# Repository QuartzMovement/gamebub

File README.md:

<p align="center">
  
</p>

**Game Bub** is an open-source FPGA retro emulation handheld, with support for Game Boy, Game Boy Color, and Game Boy Advance games.

You can buy your own, prebuilt Game Bub from **[Crowd Supply](https://www.crowdsupply.com/second-bedroom/game-bub)**!

You can find the [user guide and documentation here](https://docs.gamebub.net/).

Want to chat about Game Bub? Feel free to [join the Discord](https://discord.gg/T5xrYpMfN7).

Check out the [announcement blog post](https://eli.lipsitz.net/posts/introducing-gamebub/) for an in-depth look at the development process!

## Features
* Play physical Game Boy / Color / Advance cartridges
* Load and play ROM files from a microSD card (with built-in support for rumble, clock, accelerometer, gyroscope)
* Multiplayer link cable functionality
* Custom, from-scratch Game Boy and Game Boy Advance FPGA cores with great game compatibility
* 14+ hour battery life 
* Video output to TV or monitor via Game Bub Dock
* Extensible hardware, designed for future improvements

## Building

Building a Game Bub handheld requires manufacturing PCBs, 3D printing the shell and buttons, and assembling components from a variety of sources. For information on manufacturing and assembling your own, see [docs/building.md](docs/building.md).

For other inquiries, contact us at support@gamebub.net.

## Architecture

For an in-depth description of the project architecture, see [docs/architecture.md](docs/architecture.md).

The Game Bub handheld consists of a Xilinx XC7A100T FPGA to do the main emulation and I/O, and an ESP32-S3 microcontroller to do auxiliary tasks (configuring the FPGA, rendering the UI, loading ROM files from a microSD card and sending it to the FPGA).

### Directory Structure

* `fpga`: FPGA source code (HDL), written in [Chisel](https://github.com/chipsalliance/chisel)
* `firmware`: Microcontroller firmware

## License

Unless otherwise specified:

* Firmware (in `firmware/`) and scripts (in `scripts/`) are licensed under GPLv3 (`GPL-3.0-only`).
* FPGA source code (in `fpga/`) is licensed under the CERN Open Hardware License Version 2 - Strongly Reciprocal (`CERN-OHL-S-2.0`)
* PCB (schematic and layout), mechanical, and hardware design files are licensed under the CERN Open Hardware License Version 2 - Strongly Reciprocal (`CERN-OHL-S-2.0`)

At a high level, this means that you can copy, share, and modify the source code, as long as you provide proper attribution and share your source code / design files with the same license. However, the "Game Bub" name and logo are trademarked, and you may not use them for your product without permission.

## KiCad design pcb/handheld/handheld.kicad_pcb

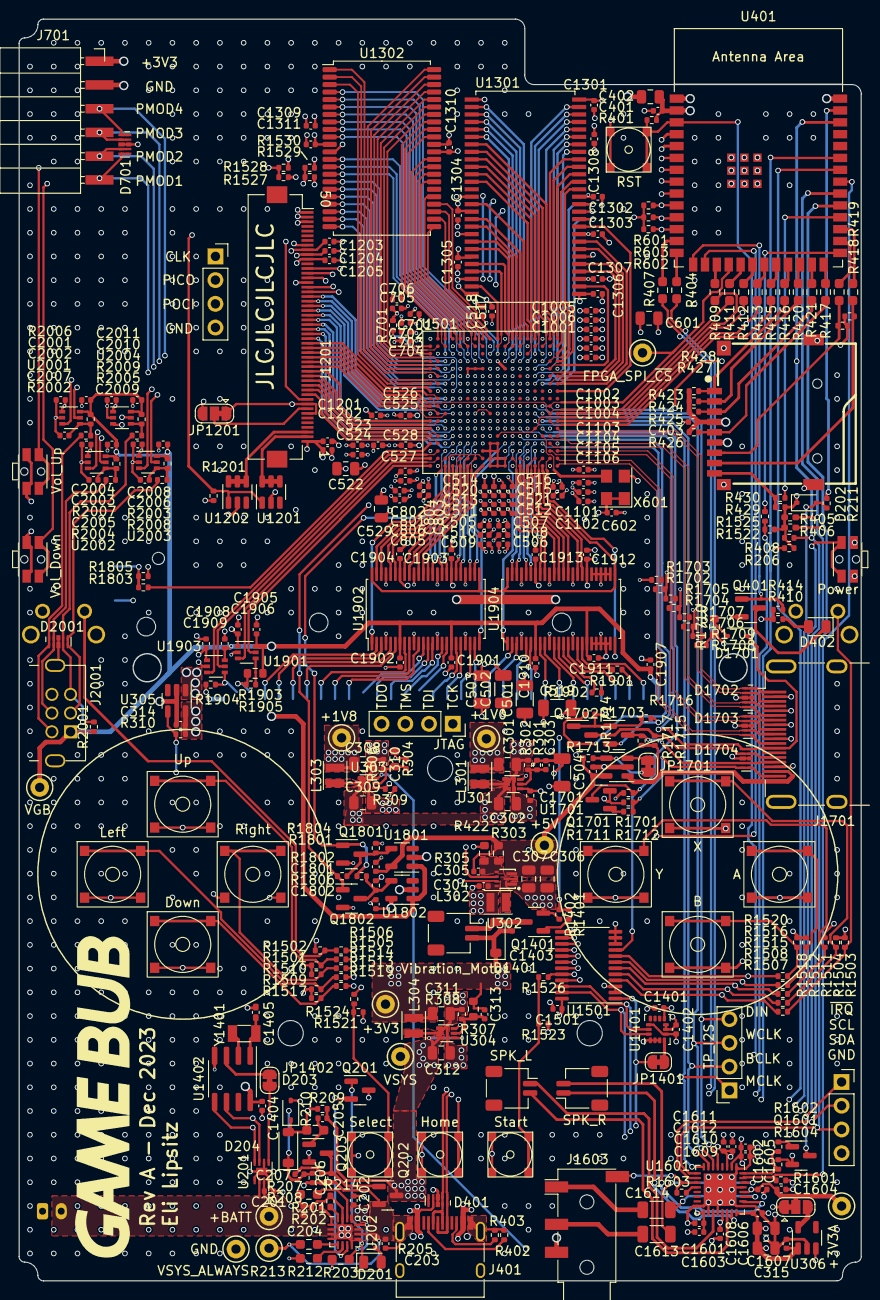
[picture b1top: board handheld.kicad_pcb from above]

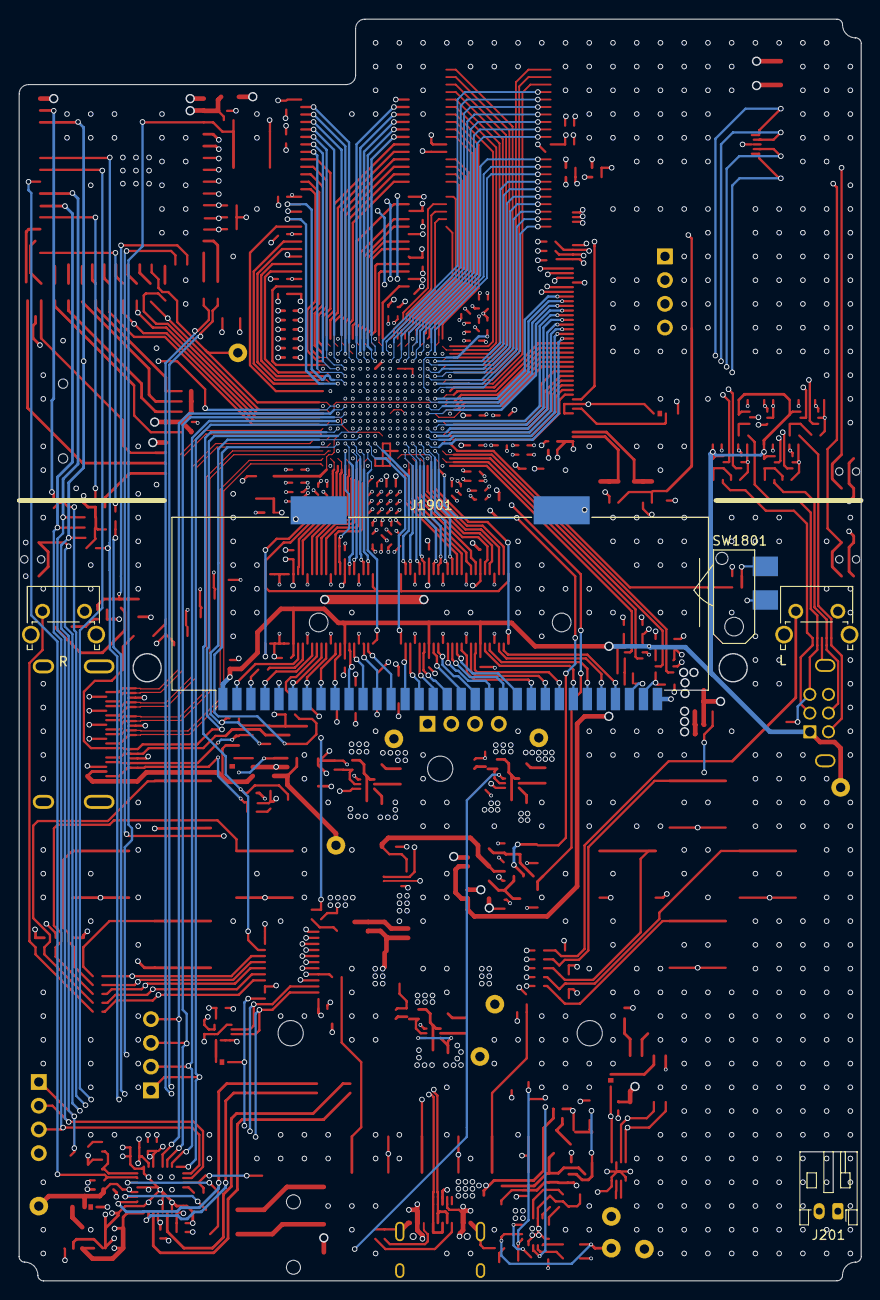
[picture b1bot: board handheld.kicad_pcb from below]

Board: 6 copper layers, 90.1 x 135.0 mm, 386 parts (5 on the bottom side), 364 nets.

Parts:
C201, C206, C314, C401, C403, C602, C1201, C1202, C1203, C1204, C1205, C1301, C1302, C1303, C1304, C1305, C1306, C1307, C1310, C1311, C1401, C1402, C1403, C1404, C1501, C1602, C1604, C1606, C1608, C1610, C1612, C1701, C1801, C1802, C1901, C1902, C1903, C1904, C1905, C1906, C1907, C1908, C1909, C1910, C1911, C1912, C1913, C2001, C2002, C2003, C2004, C2008, C2009, C2010, C2011: 100n; C_0402_1005Metric
C202, C203, C204, C505, C506, C507, C508, C509, C510, C523, C524, C705, C706, C805, C806, C1005, C1006, C1105, C1106: 4u7; C_0402_1005Metric
C205, C304, C315, C1308, C1309, C1601, C1603, C1609, C1611: 10u; C_0402_1005Metric
C207: 1u; C_0402_1005Metric
C301, C302, C308, C309, C311, C312, C522, C529, C601: 47u; C_0805_2012Metric
C303, C310, C313: 22p; C_0402_1005Metric
C305: 470p; C_0402_1005Metric
C306, C307, C402, C1605, C1607: 22u; C_0805_2012Metric
C501, C502, C503, C504, C519, C1613, C1614: 100u; C_1206_3216Metric
C511, C512, C513, C514, C515, C516, C517, C518, C520, C521, C525, C526, C527, C528, C701, C702, C703, C704, C801, C802, C803, C804, C1001, C1002, C1003, C1004, C1101, C1102, C1103, C1104: 470n; C_0402_1005Metric
C1405: 22p; C_0402_1005Metric_Pad0.74x0.62mm_HandSolder
C2005, C2006, C2007: 100p; C_0402_1005Metric
D201: CHARGE_LED; LED_0805_2012Metric
D202, D203, D1701: D_Schottky; D_SOD-323
D204, D1401: 1N4148W; D_SOD-123
D401, D701, D1702, D1703, D1704, D2001: H5VU25U; Diodes_UDFN-10_1.0x2.5mm_P0.5mm
D402: STATUS_LED; LED_0805_2012Metric
H101, H102, H103: MountingHole; MountingHole_2.7mm_M2.5
J201: Batt_Conn; JST_PH_S2B-PH-K_1x02_P2.00mm_Horizontal
J401: USB_C_Receptacle_USB2.0; USB_C_Receptacle_HRO_TYPE-C-31-M-12
J402: Micro_SD_Card_Det1; microSD_G-Switch_GT-TF003-H0185-02
J403: TP_I2C; PinSocket_1x04_P2.54mm_Vertical
J404: TP_SPI; PinSocket_1x04_P2.54mm_Vertical
J601: JTAG; PinSocket_1x04_P2.54mm_Vertical
J701: PMOD; PinSocket_1x06_P2.54mm_Horizontal_SMD
J1201: Hirose_FH12S-50S-0.5SH_1x50-1MP_P0.50mm_Horizontal_FLIPPED
J1401: Vibration_Motor; JST_SH_SM02B-SRSS-TB_1x02-1MP_P1.00mm_Horizontal
J1601: SPK_L; JST_SH_SM02B-SRSS-TB_1x02-1MP_P1.00mm_Horizontal
J1602: SPK_R; JST_SH_SM02B-SRSS-TB_1x02-1MP_P1.00mm_Horizontal
J1603: Headphone Jack; Jack_3.5mm_PJ320D_Horizontal
J1604: TP_I2S; PinSocket_1x04_P2.54mm_Vertical
J1701: HDMI_A; HDMI_A_Molex_208658-1001_Horizontal
J1901: Cartridge_Slot; GameBoy_Cartridge_AGS_1x32-1MP_P1.50mm_Socket_Horizontal
J2001: Link_Port; GameBoy_LinkPort_AGB_Horizontal
JP301: 3V3A_Jumper; SolderJumper-3_P1.3mm_Bridged12_RoundedPad1.0x1.5mm
JP1201: SolderJumper_3_Bridged12; SolderJumper-3_P1.3mm_Bridged12_RoundedPad1.0x1.5mm
JP1401, JP1402, JP1701: SolderJumper_2_Bridged; SolderJumper-2_P1.3mm_Bridged_RoundedPad1.0x1.5mm
L301, L302, L303, L304: 1u; L_Sunlord_SWPA252012S
Q201, Q203, Q401, Q1401, Q1601, Q1701, Q1702, Q1703, Q1801, Q1802: AO3400A; SOT-23
Q202: AO3401A; SOT-23
R201: 47K; R_0603_1608Metric_Pad0.98x0.95mm_HandSolder
R202, R207, R301, R401, R408, R422, R423, R424, R425, R426, R427, R428, R429, R430, R1201, R1402, R1501, R1502, R1503, R1504, R1505, R1506, R1507, R1508, R1509, R1510, R1511, R1512, R1513, R1514, R1515, R1516, R1517, R1518, R1519, R1520, R1521, R1522, R1523, R1524, R1525, R1526, R1527, R1528, R1529, R1530, R1604, R1711, R1712, R1801, R1803, R1804, R1805, R2006, R2007, R2008, R2009: 10K; R_0402_1005Metric
R203: 1K1; R_0603_1608Metric_Pad0.98x0.95mm_HandSolder
R205, R410, R1603: 2K2; R_0402_1005Metric
R206, R208, R209, R309, R310, R414, R1601, R1713, R1802, R1806, R1904, R2001: 100K; R_0402_1005Metric
R210: 470K; R_0603_1608Metric_Pad0.98x0.95mm_HandSolder
R211, R701, R1401, R1602, R1714, R1716: 1K; R_0402_1005Metric
R212, R213, R404, R407, R409, R411, R412, R413, R415, R416, R417, R418, R419, R420, R421: 0R; R_0603_1608Metric_Pad0.98x0.95mm_HandSolder
R214: 1K; R_0402_1005Metric_Pad0.72x0.64mm_HandSolder
R302, R306, R308: 15K; R_0402_1005Metric
R303: 220K; R_0603_1608Metric
R304, R305: 30K; R_0603_1608Metric
R307: 68K; R_0603_1608Metric
R402, R403: 5K1; R_0402_1005Metric
R405, R406: 3K3; R_0402_1005Metric_Pad0.72x0.64mm_HandSolder
R601, R602, R603, R1701: 4K7; R_0402_1005Metric
R1702, R1703, R1704, R1705, R1706, R1707, R1708, R1709, R1901, R1902, R1905: 49R9; R_0402_1005Metric
R1710, R1903: 27K; R_0603_1608Metric
R1715, R1717: 1K5; R_0402_1005Metric
R2002, R2003, R2004, R2005: 330R; R_0402_1005Metric
SW201: Power; SW_SPST_SKSC
SW401: RST; SW_SPST_SKRB
SW1501: Up; SW_SPST_SKRR
SW1502: L; SW_Tactile_SPST_Angled_TL1105VFxxxx
SW1503: R; SW_Tactile_SPST_Angled_TL1105VFxxxx
SW1504: X; SW_SPST_SKRR
SW1505: Left; SW_SPST_SKRR
SW1506: Right; SW_SPST_SKRR
SW1507: Y; SW_SPST_SKRR
SW1508: A; SW_SPST_SKRR
SW1509: Down; SW_SPST_SKRR
SW1510: B; SW_SPST_SKRR
SW1511: Select; SW_SPST_SKRB
SW1512: Home; SW_SPST_SKRB
SW1513: Start; SW_SPST_SKRB
SW1514: Vol_Up; SW_SPST_SKSC
SW1515: Vol_Down; SW_SPST_SKSC
SW1801: SW_Cartridge; JJOV0UL650NONPRBK_SIDE
TP201: +BATT; TestPoint_Keystone_5000-5004_Miniature
TP202: VSYS_ALWAYS; TestPoint_Keystone_5000-5004_Miniature
TP203: VSYS; TestPoint_Keystone_5000-5004_Miniature
TP301: +1V0; TestPoint_Keystone_5000-5004_Miniature
TP302: +1V8; TestPoint_Keystone_5000-5004_Miniature
TP303: +3V3; TestPoint_Keystone_5000-5004_Miniature
TP304: +3V3A; TestPoint_Keystone_5000-5004_Miniature
TP305: +5V; TestPoint_Keystone_5000-5004_Miniature
TP306: GND; TestPoint_Keystone_5000-5004_Miniature
TP401: FPGA_SPI_~{CS}; TestPoint_Keystone_5000-5004_Miniature
TP1801: VGB; TestPoint_Keystone_5000-5004_Miniature
U201: MAX17048; TDFN-8-1EP_2x2mm_P0.5mm_EP0.8x1.2mm
U202: BQ24073RGT; VQFN-16-1EP_3x3mm_P0.5mm_EP1.6x1.6mm
U301, U303, U304: TLV62585PDRL; SOT-563
U302: TPS61022RWUR; VQFN-7_L2.0-W2.0-P0.55-TL_RWU
U305, U1701, U1801, U1802: AP2191W; SOT-23-5
U306: LP5907MFX-3.3; SOT-23-5
U401: ESP32-S3-WROOM-1
U501: XC7A100T-CSG324; Xilinx_CSG324
U1201, U1202: AP2502; SOT-23-6
U1301: W9825G6KH-6; TSOP-II-54_22.2x10.16mm_P0.8mm
U1302: IS61WV25616EDBLL-10TLI; TSOP-II-44_10.16x18.41mm_P0.8mm
U1401: LSM6DS3TR-C; LGA-14_3x2.5mm_P0.5mm_LayoutBorder3x4y
U1402: PCF8563T; SOIC-8_3.9x4.9mm_P1.27mm
U1501: TCA9535PWR; TSSOP-24_4.4x7.8mm_P0.65mm
U1601: TLV320DAC3101; VQFN-32-1EP_5x5mm_P0.5mm_EP3.5x3.5mm
U1901, U1903, U2001, U2002, U2003, U2004: 74LVC1T45; SOT-363_SC-70-6
U1902, U1904: 74LVCH16T245; TSSOP-48_6.1x12.5mm_P0.5mm
X601: YSO110TR 50MHz; Oscillator_SMD_SeikoEpson_SG8002CE-4Pin_3.2x2.5mm
Y1401: 32.768kHz; Crystal_SMD_3215-2Pin_3.2x1.5mm

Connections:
+1V0: C301.1, C303.2, C501.1, C502.1, C503.1, C504.1, C505.1, C506.1, C507.1, C508.1, C509.1, C510.1, C511.1, C512.1, C513.1, C514.1, C515.1, C516.1, C517.1, C518.1, C519.1, C520.1, C521.1, L301.2, R301.1, TP301.1, U501.F8 (VCCINT), U501.F10 (VCCBRAM), U501.G7 (VCCINT), U501.G9 (VCCINT), U501.G11 (VCCBRAM), U501.H8 (VCCINT), U501.J7 (VCCINT), U501.J11 (VCCINT), U501.K8 (VCCINT), U501.L7 (VCCINT), U501.L11 (VCCINT), U501.M8 (VCCINT), U501.M10 (VCCINT), U501.N7 (VCCINT), U501.N9 (VCCINT), U501.N11 (VCCINT)
+1V8: C308.1, C310.2, C522.1, C523.1, C524.1, C525.1, C526.1, C527.1, C528.1, C1609.1, C1610.2, L303.2, R304.1, TP302.1, U501.F12 (VCCAUX), U501.H10 (VCCADC_0), U501.H12 (VCCAUX), U501.K12 (VCCAUX), U501.M12 (VCCAUX), U1601.3 (DVDD)
+3V3: C311.1, C313.2, C314.2, C401.2, C402.1, C403.2, C1201.2, C1202.2, C1203.2, C1204.2, C1205.2, C1401.1, C1402.2, C1403.2, C1501.1, C1802.2, D202.1 (K), D1401.1 (K), J402.4 (VDD), J1201.1 (LEDA), J1201.7 (IM0), J1201.9 (IM2), J1201.40 (VDDI), J1201.41 (VDDI), J1201.42 (VCI), J1401.2, JP1201.1 (A), L304.2, R206.1, R307.1, R310.1, R401.1, R405.1, R406.1, R408.1, R410.1, R414.1, R423.1, R424.1, R425.1, R426.1, R427.1, R428.1, R429.2, R1501.1, R1502.1, R1503.1, R1504.1, R1509.1, R1510.1, R1511.1, R1512.1, R1517.1, R1518.1, R1521.1, R1522.1, R1523.1, R1527.1, R1529.1, TP303.1, U305.5 (IN), U401.2 (3V3), U1401.5 (VDDIO), U1401.8 (VDD), U1401.12 (CS), U1501.24 (VCC), U1802.5 (IN)
+3V3A_DAC: C1601.1, C1602.2, C1603.1, C1604.2, JP301.2 (C), TP304.1, U1601.17 (AVDD), U1601.28 (HPVDD)
+3V3_FPGA: C529.1, C601.1, C602.2, C701.1, C702.1, C703.1, C704.1, C705.1, C706.1, C801.1, C802.1, C803.1, C804.1, C805.1, C806.1, C1001.1, C1002.1, C1003.1, C1004.1, C1005.1, C1006.1, C1101.1, C1102.1, C1103.1, C1104.1, C1105.1, C1106.1, C1301.2, C1302.2, C1303.2, C1304.2, C1305.2, C1306.2, C1307.2, C1308.1, C1309.1, C1310.2, C1311.2, C1611.1, C1612.2, C1903.2, C1904.2, C1906.2, C1909.2, C1912.2, C1913.2, C2002.2, C2004.2, C2009.2, C2011.2, J701.1, JP301.1 (A), Q1702.1 (G), Q1703.1 (G), R601.2, R602.2, R603.2, R701.2, R1701.2, R1702.1, R1703.1, R1704.1, R1705.1, R1706.1, R1707.1, R1708.1, R1709.1, R1710.1, R1714.2, R1716.2, R1904.1, SW1801.2 (B), U305.1 (OUT), U501.A7 (VCCO_35), U501.A17 (VCCO_15), U501.C3 (VCCO_35), U501.C13 (VCCO_15), U501.D6 (VCCO_35), U501.D16 (VCCO_15), U501.F2 (VCCO_35), U501.G5 (VCCO_35), U501.G15 (VCCO_15), U501.H18 (VCCO_15), U501.J1 (VCCO_35), U501.K4 (VCCO_34), U501.K14 (VCCO_15), U501.L17 (VCCO_14), U501.N3 (VCCO_34), U501.N13 (VCCO_14), U501.P6 (VCCO_34), U501.P8 (CFGBVS_0), U501.P11 (M2_0), U501.P12 (M0_0), U501.P13 (M1_0), U501.P16 (VCCO_14), U501.R9 (VCCO_0), U501.T2 (VCCO_34), U501.T12 (VCCO_14), U501.U5 (VCCO_34), U501.U15 (VCCO_14), U501.V8 (VCCO_34), U501.V18 (VCCO_14), U1301.1 (VDD), U1301.3 (VDDQ), U1301.9 (VDDQ), U1301.14 (VDD), U1301.27 (VDD), U1301.43 (VDDQ), U1301.49 (VDDQ), U1302.11 (VDD), U1302.33 (VDD), U1601.2 (IOVDD), U1901.1 (VCCA), U1902.31 (VCCA), U1902.42 (VCCA), U1903.1 (VCCA), U1904.31 (VCCA), U1904.42 (VCCA), U2001.1 (VCCA), U2002.1 (VCCA), U2003.1 (VCCA), U2004.1 (VCCA), X601.1 (Tri-State), X601.4 (VDD)
+3V3_PG: R401.2, SW401.2, U304.6 (PG), U401.3 (EN)
+5V: C305.2, C306.1, C307.1, C1701.2, C1801.2, R303.1, R1713.1, TP305.1, U302.3 (VOUT), U1701.5 (IN), U1801.5 (IN)
+BATT: C201.2, C204.1, J201.2, TP201.1, U201.2 (CELL), U201.3 (VDD), U202.2 (BAT), U202.3 (BAT)
/Audio/DAC_INT: R1602.2, R1604.1, U1601.32 (GPIO1)
/Audio/DAC_INT_R: Q1601.1 (G), R1602.1
/Audio/HeadphoneJack_Tip: C1614.2, J1603.T
/Audio/Headphone_Jack_R: C1613.2, J1603.R1
/Audio/Headphone_Left: C1614.1, U1601.27 (HPL)
/Audio/Headphone_Mic: J1603.S, R1603.2, U1601.11 (VOL/MICDET)
/Audio/Headphone_Right: C1613.1, U1601.30 (HPR)
/Audio/MICBIAS: R1603.1, U1601.12 (MICBIAS)
/Audio/Speaker_Left_M: J1601.1, U1601.19 (SPLM)
/Audio/Speaker_Left_P: J1601.2, U1601.22 (SPLP)
/Audio/Speaker_Right_M: J1602.1, U1601.23 (SPRM)
/Audio/Speaker_Right_P: J1602.2, U1601.26 (SPRP)
/Buttons/BTN_A_s: R1512.2, R1516.2, SW1508.1
/Buttons/BTN_B_s: R1518.2, R1520.2, SW1510.1
/Buttons/BTN_Down_s: R1517.2, R1519.2, SW1509.1
/Buttons/BTN_Home_s: R1522.2, R1525.2, SW1512.1
/Buttons/BTN_L_s: R1502.2, R1506.2, SW1502.1
/Buttons/BTN_Left_s: R1509.2, R1513.2, SW1505.1
/Buttons/BTN_R_s: R1503.2, R1507.2, SW1503.1
/Buttons/BTN_Right_s: R1510.2, R1514.2, SW1506.1
/Buttons/BTN_Select_s: R1521.2, R1524.2, SW1511.1
/Buttons/BTN_Start_s: R1523.2, R1526.2, SW1513.1
/Buttons/BTN_Up_s: R1501.2, R1505.2, SW1501.1
/Buttons/BTN_Vol_Down_s: R1529.2, R1530.2, SW1515.1
/Buttons/BTN_Vol_Up_s: R1527.2, R1528.2, SW1514.1
/Buttons/BTN_X_s: R1504.2, R1508.2, SW1504.1
/Buttons/BTN_Y_s: R1511.2, R1515.2, SW1507.1
/ESP32-S3/ESP32_SDIO_CLK: R417.1, U401.26 (GPIO45)
/ESP32-S3/ESP32_SDIO_CMD: R421.1, U401.25 (GPIO48)
/ESP32-S3/ESP32_SDIO_D0: R418.2, U401.28 (GPIO35)
/ESP32-S3/ESP32_SDIO_D1: R419.2, U401.29 (GPIO36)
/ESP32-S3/ESP32_SDIO_D2: R416.1, U401.23 (GPIO21)
/ESP32-S3/ESP32_SDIO_D3: R420.1, U401.24 (GPIO47)
/ESP32-S3/ESP32_SPI2_CLK: R412.1, U401.20 (GPIO12)
/ESP32-S3/ESP32_SPI2_D0: R411.1, U401.19 (GPIO11)
/ESP32-S3/ESP32_SPI2_D1: R413.1, U401.21 (GPIO13)
/ESP32-S3/ESP32_SPI2_D2: R415.1, U401.22 (GPIO14)
/ESP32-S3/ESP32_SPI2_D3: R409.1, U401.17 (GPIO9)
/ESP32-S3/ESP32_USB_D+: R404.1, U401.14 (GPIO20/USB_D+)
/ESP32-S3/ESP32_USB_D-: R407.1, U401.13 (GPIO19/USB_D-)
/ESP32-S3/SDIO_CLK: J402.5 (CLK), R417.2, R426.2
/ESP32-S3/SDIO_CMD: J402.3 (CMD), R421.2, R425.2
/ESP32-S3/SDIO_D0: J402.7 (DAT0), R418.1, R427.2
/ESP32-S3/SDIO_D1: J402.8 (DAT1), R419.1, R428.2
/ESP32-S3/SDIO_D2: J402.1 (DAT2), R416.2, R423.2
/ESP32-S3/SDIO_D3/~CS: J402.2 (DAT3/CD), R420.2, R424.2
/ESP32-S3/SD_Detect: R430.2, U401.30 (GPIO37)
/ESP32-S3/SD_Detect_s: J402.9 (DET), R429.1, R430.1
/ESP32-S3/STATUS_LED: Q401.1 (G), R414.2, U401.15 (GPIO3)
/ESP32-S3/Status_LED_A: D402.2 (A), R410.2
/ESP32-S3/Status_LED_K: D402.1 (K), Q401.3 (D)
/ESP32-S3/USB_CC1: J401.A5 (CC1), R402.1
/ESP32-S3/USB_CC2: J401.B5 (CC2), R403.1
/ESP32-S3/USB_D+: D401.1 (K1), D401.10 (K1), J401.A6 (D+), J401.B6 (D+), R404.2
/ESP32-S3/USB_D-: D401.2 (K2), D401.9 (K2), J401.A7 (D-), J401.B7 (D-), R407.2
/FPGA Config/FPGA_JTAG_TCK: J601.1, U501.E10 (TCK_0)
/FPGA Config/FPGA_JTAG_TDI: J601.2, U501.E11 (TDI_0)
/FPGA Config/FPGA_JTAG_TDO: J601.4, U501.E13 (TDO_0)
/FPGA Config/FPGA_JTAG_TMS: J601.3, U501.E12 (TMS_0)
/FPGA IO Bank 14/FPGA_PUDC_B: R701.1, U501.L15 (IO_L3P_T0_DQS_PUDC_B_14)
/FPGA IO Bank 14/PMOD_1: D701.5 (K4), D701.6 (K4), J701.6, U501.M14 (IO_L2N_T0_D03_14)
/FPGA IO Bank 14/PMOD_2: D701.4 (K3), D701.7 (K3), J701.5, U501.N14 (IO_L8P_T1_D11_14)
/FPGA IO Bank 14/PMOD_3: D701.2 (K2), D701.9 (K2), J701.4, U501.P14 (IO_L8N_T1_D12_14)
/FPGA IO Bank 14/PMOD_4: D701.1 (K1), D701.10 (K1), J701.3, U501.M13 (IO_L6N_T0_D08_VREF_14)
/FPGA IO Bank 16/BANK16_VCCO: U501.A8 (IO_L12N_T1_MRCC_16), U501.A9 (IO_L14N_T2_SRCC_16), U501.A10 (IO_L14P_T2_SRCC_16), U501.B8 (IO_L12P_T1_MRCC_16), U501.B9 (IO_L11N_T1_SRCC_16), U501.B10 (VCCO_16), U501.C9 (IO_L11P_T1_SRCC_16), U501.C10 (IO_L13N_T2_MRCC_16), U501.C11 (IO_L13P_T2_MRCC_16), U501.D9 (IO_L6N_T0_VREF_16), U501.D10 (IO_L19N_T3_VREF_16)
/Game Boy Interfaces/Game Boy Cartridge/Cart_A16: J1901.22 (A16/D0), U1902.12 (1B8)
/Game Boy Interfaces/Game Boy Cartridge/Cart_A17: J1901.23 (A17/D1), U1902.11 (1B7)
/Game Boy Interfaces/Game Boy Cartridge/Cart_A18: J1901.24 (A18/D2), U1902.9 (1B6)
/Game Boy Interfaces/Game Boy Cartridge/Cart_A19: J1901.25 (A19/D3), U1902.8 (1B5)
/Game Boy Interfaces/Game Boy Cartridge/Cart_A20: J1901.26 (A20/D4), U1902.6 (1B4)
/Game Boy Interfaces/Game Boy Cartridge/Cart_A21: J1901.27 (A21/D5), U1902.5 (1B3)
/Game Boy Interfaces/Game Boy Cartridge/Cart_A22: J1901.28 (A22/D6), U1902.3 (1B2)
/Game Boy Interfaces/Game Boy Cartridge/Cart_A23: J1901.29 (A23/D7), U1902.2 (1B1)
/Game Boy Interfaces/Game Boy Cartridge/Cart_AD0: J1901.6 (AD0/A0), U1904.12 (1B8)
/Game Boy Interfaces/Game Boy Cartridge/Cart_AD1: J1901.7 (AD1/A1), U1904.11 (1B7)
/Game Boy Interfaces/Game Boy Cartridge/Cart_AD2: J1901.8 (AD2/A2), U1904.9 (1B6)
/Game Boy Interfaces/Game Boy Cartridge/Cart_AD3: J1901.9 (AD3/A3), U1904.8 (1B5)
/Game Boy Interfaces/Game Boy Cartridge/Cart_AD4: J1901.10 (AD4/A4), U1904.6 (1B4)
/Game Boy Interfaces/Game Boy Cartridge/Cart_AD5: J1901.11 (AD5/A5), U1904.5 (1B3)
/Game Boy Interfaces/Game Boy Cartridge/Cart_AD6: J1901.12 (AD6/A6), U1904.3 (1B2)
/Game Boy Interfaces/Game Boy Cartridge/Cart_AD7: J1901.13 (AD7/A7), U1904.2 (1B1)
/Game Boy Interfaces/Game Boy Cartridge/Cart_AD8: J1901.14 (AD8/A8), U1902.23 (2B8)
/Game Boy Interfaces/Game Boy Cartridge/Cart_AD9: J1901.15 (AD9/A9), U1902.22 (2B7)
/Game Boy Interfaces/Game Boy Cartridge/Cart_AD10: J1901.16 (AD10/A10), U1902.20 (2B6)
/Game Boy Interfaces/Game Boy Cartridge/Cart_AD11: J1901.17 (AD11/A11), U1902.19 (2B5)
/Game Boy Interfaces/Game Boy Cartridge/Cart_AD12: J1901.18 (AD12/A12), U1902.17 (2B4)
/Game Boy Interfaces/Game Boy Cartridge/Cart_AD13: J1901.19 (AD13/A13), U1902.16 (2B3)
/Game Boy Interfaces/Game Boy Cartridge/Cart_AD14: J1901.20 (AD14/A14), U1902.14 (2B2)
/Game Boy Interfaces/Game Boy Cartridge/Cart_AD15: J1901.21 (AD15/A15), U1902.13 (2B1)
/Game Boy Interfaces/Game Boy Cartridge/Cart_PHI: J1901.2 (PHI), U1904.17 (2B4)
/Game Boy Interfaces/Game Boy Cartridge/Cart_VIN: J1901.31 (~REQ/VIN), R1904.2, U1903.4 (B)
/Game Boy Interfaces/Game Boy Cartridge/Cart_~CS1: R1902.1, U1904.13 (2B1)
/Game Boy Interfaces/Game Boy Cartridge/Cart_~CS1_d: J1901.5 (~CS1/~CS), R1902.2
/Game Boy Interfaces/Game Boy Cartridge/Cart_~CS2: R1905.2, U1901.4 (B)
/Game Boy Interfaces/Game Boy Cartridge/Cart_~CS2_d: J1901.30 (~CS2/~RES), R1903.2, R1905.1
/Game Boy Interfaces/Game Boy Cartridge/Cart_~RD: J1901.4 (~RD), U1904.14 (2B2)
/Game Boy Interfaces/Game Boy Cartridge/Cart_~WR: R1901.2, U1904.16 (2B3)
/Game Boy Interfaces/Game Boy Cartridge/Cart_~WR_d: J1901.3 (~WR), R1901.1
/Game Boy Interfaces/Game Boy Link/Link_SC: R2005.2, R2009.2, U2004.4 (B)
/Game Boy Interfaces/Game Boy Link/Link_SC_a: D2001.4 (K3), D2001.7 (K3), J2001.5 (SC), R2001.2, R2005.1
/Game Boy Interfaces/Game Boy Link/Link_SD: C2005.1, R2004.2, R2007.2, U2002.4 (B)
/Game Boy Interfaces/Game Boy Link/Link_SD_a: D2001.2 (K2), D2001.9 (K2), J2001.4 (SD), R2004.1
/Game Boy Interfaces/Game Boy Link/Link_SI: C2006.1, R2003.2, R2008.2, U2003.4 (B)
/Game Boy Interfaces/Game Boy Link/Link_SI_a: D2001.5 (K4), D2001.6 (K4), J2001.3 (SI), R2003.1
/Game Boy Interfaces/Game Boy Link/Link_SO: C2007.1, R2002.2, R2006.2, U2001.4 (B)
/Game Boy Interfaces/Game Boy Link/Link_SO_a: D2001.1 (K1), D2001.10 (K1), J2001.2 (SO), R2002.1
/Game Boy Interfaces/SW_Cartridge_s: R1803.2, R1805.1, SW1801.1 (A)
/Game Boy Interfaces/VGB_3V3_SW_En: Q1802.3 (D), R1804.2, R1806.2, U1802.4 (EN)
/Game Boy Interfaces/VGB_5V_SW_En: Q1801.3 (D), R1801.2, R1802.2, U1801.4 (EN)
/HDMI/HDMI_5V_EN: JP1701.1 (A), R1713.2, U1701.4 (EN)
/HDMI/HDMI_5V_FLG: JP1701.2 (B), U1701.3 (~FLG)
/HDMI/HDMI_+5V: J1701.18 (+5V), R1715.1, R1717.1, U1701.1 (OUT)
/HDMI/HDMI_CEC_DA: D1701.2 (A), R1710.2
/HDMI/HDMI_HPD: D1704.5 (K4), D1704.6 (K4), J1701.19 (HPD), R1711.2, R1712.1
/HDMI/HDMI_HPD_g: Q1701.1 (G), R1711.1
/HDMI/HDMI_SCL_LS: D1704.2 (K2), D1704.9 (K2), J1701.15 (SCL), Q1702.3 (D), R1715.2
/HDMI/HDMI_SDA_LS: D1704.4 (K3), D1704.7 (K3), J1701.16 (SDA), Q1703.3 (D), R1717.2
/LCD/Backlight_Cathode_1: J1201.2 (LEDK), U1201.4 (LED3), U1201.5 (LED2), U1201.6 (LED1)
/LCD/Backlight_Cathode_2: J1201.3 (LEDK), U1202.4 (LED3), U1202.5 (LED2), U1202.6 (LED1)
/LCD/LCD_IM1: J1201.8 (IM1), JP1201.2 (C)
/Peripherals/IMU_INT: JP1401.1 (A), U1401.4 (INT1)
/Peripherals/RTC_INT: JP1402.1 (A), U1402.3 (~INT)
/Peripherals/RTC_OSCI: C1405.2, U1402.1 (OSCI), Y1401.1
/Peripherals/RTC_OSCO: U1402.2 (OSCO), Y1401.2
/Peripherals/Vibrate_FET_g: Q1401.1 (G), R1401.2
/Peripherals/Vibrate_N: C1403.1, D1401.2 (A), J1401.1, Q1401.3 (D)
/Power Path/BTN_Power_s: C207.2, D204.1 (K), R207.2, SW201.1
/Power Path/Charge_LED_A: D201.2 (A), R205.2
/Power Path/PWR_EN1: R212.2, U202.6 (EN1)
/Power Path/PWR_EN2: R213.2, U202.5 (EN2)
/Power Path/PWR_ILIM: R203.1, U202.12 (ILIM)
/Power Path/PWR_ISET: R214.2, U202.16 (ISET)
/Power Path/PWR_SW_nFET_g: C205.2, Q203.1 (G), R210.1
/Power Path/PWR_SW_pFET_g: C206.2, C207.1, Q202.1 (G), Q203.3 (D), R208.2
/Power Path/PWR_TMR: R201.1, U202.14 (TMR)
/Power Path/PWR_TS: R202.1, U202.1 (TS)
/Power Path/~CHG: D201.1 (K), Q201.1 (G), U202.9 (~CHG)
/Power Path/~POWER_SW_a: D202.2 (A), D203.1 (K), D204.2 (A), R209.2, R210.2, R211.1
/Power Regulators/+1V0_PG: R309.2, U301.6 (PG), U303.4 (EN)
/Power Regulators/+1V8_PG: R310.2, U303.6 (PG), U305.4 (EN), U306.3 (EN)
/Power Regulators/Boost_5V_FB: C305.1, R303.2, R305.1, U302.4 (FB)
/Power Regulators/Boost_5V_SW: L302.2, U302.2 (SW)
/Power Regulators/Buck_1V0_FB: C303.1, R301.2, R302.1, U301.5 (FB)
/Power Regulators/Buck_1V0_SW: L301.1, U301.2 (SW)
/Power Regulators/Buck_1V8_FB: C310.1, R304.2, R306.1, U303.5 (FB)
/Power Regulators/Buck_1V8_SW: L303.1, U303.2 (SW)
/Power Regulators/Buck_3V3_FB: C313.1, R307.2, R308.1, U304.5 (FB)
/Power Regulators/Buck_3V3_SW: L304.1, U304.2 (SW)
/Power Regulators/LDO_+3V3_Out: JP301.3 (B), U306.5 (OUT)
BATT_CHG: Q201.3 (D), R206.2, U401.35 (GPIO42/MTMS)
BTN_A: R1516.1, U501.N5 (IO_L13P_T2_MRCC_34), U1501.7 (P03)
BTN_B: R1520.1, U501.P5 (IO_L13N_T2_MRCC_34), U1501.8 (P04)
BTN_Down: R1519.1, U501.H5 (IO_L24N_T3_35), U1501.18 (P15)
BTN_Home: R1525.1, U401.27 (GPIO0/BOOT)
BTN_L: R1506.1, U501.H6 (IO_L24P_T3_35), U1501.14 (P11)
BTN_Left: R1513.1, U501.G6 (IO_L19P_T3_35), U1501.17 (P14)
BTN_R: R1507.1, U501.L5 (IO_L6N_T0_VREF_34), U1501.4 (P00)
BTN_Right: R1514.1, U501.F5 (IO_0_35), U1501.16 (P13)
BTN_Select: R1524.1, U501.J5 (IO_25_35), U1501.19 (P16)
BTN_Start: R1526.1, U501.K5 (IO_L5P_T0_34), U1501.20 (P17)
BTN_Up: R1505.1, U501.E5 (IO_L5N_T0_AD13N_35), U1501.15 (P12)
BTN_VOL_DOWN: R1530.1, U401.5 (GPIO5)
BTN_VOL_UP: R1528.1, U401.4 (GPIO4)
BTN_X: R1508.1, U501.L6 (IO_L6P_T0_34), U1501.5 (P01)
BTN_Y: R1515.1, U501.M6 (IO_L18P_T2_34), U1501.6 (P02)
DAC_BCLK: J1604.2, U501.G3 (IO_L20N_T3_35), U1601.7 (BCLK)
DAC_DIN: J1604.4, U501.J4 (IO_L21P_T3_DQS_35), U1601.5 (DIN)
DAC_MCLK: J1604.1, U501.G4 (IO_L20P_T3_35), U1601.8 (MCLK)
DAC_WCLK: J1604.3, U501.H4 (IO_L21N_T3_DQS_35), U1601.6 (WCLK)
DAC_~RESET: R1601.1, U401.33 (GPIO40/MTDO), U1601.31 (~RESET)
FPGA_CLK_50MHz: U501.E3 (IO_L12P_T1_MRCC_35), X601.3 (OUT)
FPGA_DONE: R601.1, U401.10 (GPIO17), U501.P10 (DONE_0)
FPGA_INIT_B: R602.1, U401.12 (GPIO8), U501.P7 (INIT_B_0)
FPGA_POWER_EN: R422.1, U301.4 (EN), U302.5 (EN), U401.16 (GPIO46)
FPGA_PROGRAM_B: R603.1, U401.11 (GPIO18), U501.P9 (PROGRAM_B_0)
FPGA_SPI_~CS: TP401.1, U401.18 (GPIO10), U501.J2 (IO_L22N_T3_35)
GB_3V3_Enable: Q1801.1 (G), R1804.1, U501.B16 (IO_L7P_T1_AD2P_15)
GB_5V_Enable: Q1802.1 (G), R1801.1, U501.J13 (IO_L17N_T2_A25_15)
GB_Cart_A16: U501.A11 (IO_L4N_T0_15), U1902.37 (1A8)
GB_Cart_A17: U501.B12 (IO_L3N_T0_DQS_AD1N_15), U1902.38 (1A7)
GB_Cart_A18: U501.A13 (IO_L9P_T1_DQS_AD3P_15), U1902.40 (1A6)
GB_Cart_A19: U501.B13 (IO_L2P_T0_AD8P_15), U1902.41 (1A5)
GB_Cart_A20: U501.A14 (IO_L9N_T1_DQS_AD3N_15), U1902.43 (1A4)
GB_Cart_A21: U501.B14 (IO_L2N_T0_AD8N_15), U1902.44 (1A3)
GB_Cart_A22: U501.A15 (IO_L8P_T1_AD10P_15), U1902.46 (1A2)
GB_Cart_A23: U501.B11 (IO_L4P_T0_15), U1902.47 (1A1)
GB_Cart_AD0: U501.B6 (IO_L2N_T0_AD12N_35), U1904.37 (1A8)
GB_Cart_AD1: U501.A6 (IO_L3P_T0_DQS_AD5P_35), U1904.38 (1A7)
GB_Cart_AD2: U501.B7 (IO_L2P_T0_AD12P_35), U1904.40 (1A6)
GB_Cart_AD3: U501.C4 (IO_L7P_T1_AD6P_35), U1904.41 (1A5)
GB_Cart_AD4: U501.D4 (IO_L11N_T1_SRCC_35), U1904.43 (1A4)
GB_Cart_AD5: U501.C5 (IO_L1N_T0_AD4N_35), U1904.44 (1A3)
GB_Cart_AD6: U501.D5 (IO_L11P_T1_SRCC_35), U1904.46 (1A2)
GB_Cart_AD7: U501.C6 (IO_L1P_T0_AD4P_35), U1904.47 (1A1)
GB_Cart_AD8: U501.D8 (IO_L4P_T0_35), U1902.26 (2A8)
GB_Cart_AD9: U501.C12 (IO_L3P_T0_DQS_AD1P_15), U1902.27 (2A7)
GB_Cart_AD10: U501.D12 (IO_L6P_T0_15), U1902.29 (2A6)
GB_Cart_AD11: U501.D13 (IO_L6N_T0_VREF_15), U1902.30 (2A5)
GB_Cart_AD12: U501.C14 (IO_L1N_T0_AD0N_15), U1902.32 (2A4)
GB_Cart_AD13: U501.D14 (IO_L1P_T0_AD0P_15), U1902.33 (2A3)
GB_Cart_AD14: U501.C15 (IO_L12N_T1_MRCC_15), U1902.35 (2A2)
GB_Cart_AD15: U501.C16 (IO_L20P_T3_A20_15), U1902.36 (2A1)
GB_Cart_PHI: U501.B3 (IO_L10P_T1_AD15P_35), U1904.32 (2A4)
GB_Cart_VIN: U501.C17 (IO_L20N_T3_A19_15), U1903.3 (A)
GB_Cart_~CS1: U501.A5 (IO_L3N_T0_DQS_AD5N_35), U1904.36 (2A1)
GB_Cart_~CS2: U501.B17 (IO_L7N_T1_AD2N_15), U1901.3 (A)
GB_Cart_~OE: U501.A3 (IO_L8N_T1_AD14N_35), U1902.25 (2~OE), U1902.48 (1~OE), U1904.25 (2~OE), U1904.48 (1~OE)
GB_Cart_~RD: U501.B4 (IO_L7N_T1_AD6N_35), U1904.35 (2A2)
GB_Cart_~WR: U501.A4 (IO_L8P_T1_AD14P_35), U1904.33 (2A3)
GB_Dir_Cart0: U501.A16 (IO_L8N_T1_AD10N_15), U1902.1 (1DIR)
GB_Dir_Cart1: U501.D7 (IO_L6N_T0_VREF_35), U1902.24 (2DIR)
GB_Dir_Cart2: U501.C7 (IO_L4N_T0_35), U1904.1 (1DIR)
GB_Dir_Cart3: U501.B2 (IO_L10N_T1_AD15N_35), U1904.24 (2DIR)
GB_Dir_SC: U501.G14 (IO_L15N_T2_DQS_ADV_B_15), U2004.5 (DIR)
GB_Dir_SD: U501.F13 (IO_L5P_T0_AD9P_15), U2002.5 (DIR)
GB_Dir_SI: U501.H14 (IO_L15P_T2_DQS_15), U2003.5 (DIR)
GB_Dir_SO: U501.L14 (IO_L2P_T0_D02_14), U2001.5 (DIR)
GB_Dir_VIN: U501.B18 (IO_L10P_T1_AD11P_15), U1903.5 (DIR)
GB_Dir_~CS2: U501.A18 (IO_L10N_T1_AD11N_15), U1901.5 (DIR)
GB_Link_SC: U501.G13 (IO_0_15), U2004.3 (A)
GB_Link_SD: U501.F14 (IO_L5N_T0_AD9N_15), U2002.3 (A)
GB_Link_SI: U501.J14 (IO_L19P_T3_A22_15), U2003.3 (A)
GB_Link_SO: U501.L13 (IO_L6P_T0_FCS_B_14), U2001.3 (A)
GND: C201.1, C202.2, C203.2, C204.2, C301.2, C302.2, C304.2, C306.2, C307.2, C308.2, C309.2, C311.2, C312.2, C314.1, C315.2, C401.1, C402.2, C403.1, C501.2, C502.2, C503.2, C504.2, C505.2, C506.2, C507.2, C508.2, C509.2, C510.2, C511.2, C512.2, C513.2, C514.2, C515.2, C516.2, C517.2, C518.2, C519.2, C520.2, C521.2, C522.2, C523.2, C524.2, C525.2, C526.2, C527.2, C528.2, C529.2, C601.2, C602.1, C701.2, C702.2, C703.2, C704.2, C705.2, C706.2, C801.2, C802.2, C803.2, C804.2, C805.2, C806.2, C1001.2, C1002.2, C1003.2, C1004.2, C1005.2, C1006.2, C1101.2, C1102.2, C1103.2, C1104.2, C1105.2, C1106.2, C1201.1, C1202.1, C1203.1, C1204.1, C1205.1, C1301.1, C1302.1, C1303.1, C1304.1, C1305.1, C1306.1, C1307.1, C1308.2, C1309.2, C1310.1, C1311.1, C1401.2, C1402.1, C1404.1, C1405.1, C1501.2, C1601.2, C1602.1, C1603.2, C1604.1, C1605.2, C1606.1, C1607.2, C1608.1, C1609.2, C1610.1, C1611.2, C1612.1, C1701.1, C1801.1, C1802.1, C1901.1, C1902.1, C1903.1, C1904.1, C1905.1, C1906.1, C1907.1, C1908.1, C1909.1, C1910.1, C1911.1, C1912.1, C1913.1, C2001.1, C2002.1, C2003.1, C2004.1, C2005.2, C2006.2, C2007.2, C2008.1, C2009.1, C2010.1, C2011.1, D203.2 (A), D401.3 (A), D401.8 (A), D701.3 (A), D701.8 (A), D1702.3 (A), D1702.8 (A), D1703.3 (A), D1703.8 (A), D1704.3 (A), D1704.8 (A), D2001.3 (A), D2001.8 (A), J201.1, J401.A1 (GND), J401.A12 (GND), J401.B1 (GND), J401.B12 (GND), J401.S1 (SHIELD), J402.6 (VSS), J402.10 (SHIELD), J403.4, J404.4, J701.2, J1201.35 (RD), J1201.43 (GND), J1201.48 (GND), J1201.49 (GND), J1201.50 (GND), J1603.R2, J1701.2 (D2S), J1701.5 (D1S), J1701.8 (D0S), J1701.11 (CKS), J1701.17 (GND), J1701.SH, J1901.32 (GND), J1901.MP, J2001.6 (GND), J2001.SH, JP1201.3 (B), Q201.2 (S), Q203.2 (S), Q401.2 (S), Q1401.2 (S), Q1601.2 (S), Q1701.2 (S), Q1801.2 (S), Q1802.2 (S), R201.2, R202.2, R203.2, R212.1, R214.1, R302.2, R305.2, R306.2, R308.2, R402.2, R403.2, R422.2, R1201.2, R1402.2, R1601.2, R1604.2, R1712.2, R1802.1, R1805.2, R1806.1, SW201.2, SW401.1, SW1501.2, SW1502.2, SW1503.2, SW1504.2, SW1505.2, SW1506.2, SW1507.2, SW1508.2, SW1509.2, SW1510.2, SW1511.2, SW1512.2, SW1513.2, SW1514.2, SW1515.2, TP306.1, U201.1 (CTG), U201.4 (GND), U201.6 (QSTRT), U201.9 (EP), U202.4 (~CE), U202.8 (VSS), U202.15 (TD), U202.17 (VSS), U301.1 (GND), U302.1 (GND), U302.6 (MODE), U303.1 (GND), U304.1 (GND), U305.2 (GND), U306.2 (GND), U401.1 (GND), U401.40 (GND), U401.41 (GND), U501.A2 (GND), U501.A12 (GND), U501.B5 (GND), U501.B15 (GND), U501.C8 (GND), U501.C18 (GND), U501.D1 (GND), U501.D11 (GND), U501.E4 (GND), U501.E8 (VCCBATT_0), U501.E14 (GND), U501.F7 (GND), U501.F9 (GND), U501.F11 (GND), U501.F17 (GND), U501.G8 (GND), U501.G10 (GND), U501.G12 (GND), U501.H3 (GND), U501.H7 (GND), U501.H9 (GNDADC_0), U501.H11 (GND), U501.H13 (GND), U501.J6 (GND), U501.J8 (GND), U501.J9 (VREFN_0), U501.J10 (VP_0), U501.J12 (GND), U501.J16 (GND), U501.K7 (GND), U501.K9 (VN_0), U501.K10 (VREFP_0), U501.K11 (GND), U501.L2 (GND), U501.L8 (GND), U501.L9 (DXN_0), U501.L10 (DXP_0), U501.L12 (GND), U501.M5 (GND), U501.M7 (GND), U501.M9 (GND), U501.M11 (GND), U501.M15 (GND), U501.N8 (GND), U501.N10 (GND), U501.N12 (GND), U501.N18 (GND), U501.P1 (GND), U501.R4 (GND), U501.R14 (GND), U501.T7 (GND), U501.T17 (GND), U501.U10 (GND), U501.V3 (GND), U501.V13 (GND), U1201.2 (GND), U1202.2 (GND), U1301.6 (VSSQ), U1301.12 (VSSQ), U1301.28 (VSS), U1301.41 (VSS), U1301.46 (VSSQ), U1301.52 (VSSQ), U1301.54 (VSS), U1302.12 (GND), U1302.34 (GND), U1401.1 (SDO/SA0), U1401.2 (SDX), U1401.3 (SCX), U1401.6 (GND), U1401.7 (GND), U1402.4 (VSS), U1501.2 (A1), U1501.3 (A2), U1501.10 (P06), U1501.11 (P07), U1501.12 (GND), U1501.13 (P10), U1501.21 (A0), U1601.1 (IOVSS), U1601.16 (AVSS), U1601.18 (DVSS), U1601.20 (SPLVSS), U1601.25 (SPRVSS), U1601.29 (HPVSS), U1601.33 (EP), U1701.2 (GND), U1801.2 (GND), U1802.2 (GND), U1901.2 (GND), U1902.4 (GND), U1902.10 (GND), U1902.15 (GND), U1902.21 (GND), U1902.28 (GND), U1902.34 (GND), U1902.39 (GND), U1902.45 (GND), U1903.2 (GND), U1904.4 (GND), U1904.10 (GND), U1904.15 (GND), U1904.19 (2B5), U1904.20 (2B6), U1904.21 (GND), U1904.22 (2B7), U1904.23 (2B8), U1904.26 (2A8), U1904.27 (2A7), U1904.28 (GND), U1904.29 (2A6), U1904.30 (2A5), U1904.34 (GND), U1904.39 (GND), U1904.45 (GND), U2001.2 (GND), U2002.2 (GND), U2003.2 (GND), U2004.2 (GND), X601.2 (GND)
HDMI_CEC: D1701.1 (K), D1704.1 (K1), D1704.10 (K1), J1701.13 (CEC), U501.F6 (IO_L19N_T3_VREF_35)
HDMI_CLK+: D1703.4 (K3), D1703.7 (K3), J1701.10 (CK+), R1703.2, U501.B1 (IO_L9P_T1_DQS_AD7P_35)
HDMI_CLK-: D1703.5 (K4), D1703.6 (K4), J1701.12 (CK-), R1702.2, U501.A1 (IO_L9N_T1_DQS_AD7N_35)
HDMI_D0+: D1703.1 (K1), D1703.10 (K1), J1701.7 (D0+), R1705.2, U501.C1 (IO_L16N_T2_35)
HDMI_D0-: D1703.2 (K2), D1703.9 (K2), J1701.9 (D0-), R1704.2, U501.C2 (IO_L16P_T2_35)
HDMI_D1+: D1702.4 (K3), D1702.7 (K3), J1701.4 (D1+), R1707.2, U501.E2 (IO_L14P_T2_SRCC_35)
HDMI_D1-: D1702.5 (K4), D1702.6 (K4), J1701.6 (D1-), R1706.2, U501.D2 (IO_L14N_T2_SRCC_35)
HDMI_D2+: D1702.1 (K1), D1702.10 (K1), J1701.1 (D2+), R1709.2, U501.F1 (IO_L18P_T2_35)
HDMI_D2-: D1702.2 (K2), D1702.9 (K2), J1701.3 (D2-), R1708.2, U501.E1 (IO_L18N_T2_35)
HDMI_SCL: Q1702.2 (S), R1714.1, U501.D3 (IO_L12N_T1_MRCC_35)
HDMI_SDA: Q1703.2 (S), R1716.1, U501.E6 (IO_L5P_T0_AD13P_35)
HDMI_~HPD: Q1701.3 (D), R1701.1, U501.F3 (IO_L13N_T2_MRCC_35), U1501.9 (P05)
I2C0_SCL: J403.2, R405.2, U201.7 (SCL), U401.32 (GPIO39/MTCK), U1401.13 (SCL), U1402.6 (SCL), U1501.22 (SCL), U1601.10 (SCL)
I2C0_SDA: J403.3, R406.2, U201.8 (SDA), U401.31 (GPIO38), U1401.14 (SDA), U1402.5 (SDA), U1501.23 (SDA), U1601.9 (SDA)
LCD_BACKLIGHT: R1201.1, U401.6 (GPIO6), U1201.1 (EN), U1202.1 (EN)
LCD_DATA_EN: J1201.14 (DE), U501.F18 (IO_L22N_T3_A16_15)
LCD_DB0: J1201.32 (DB0), U501.K16 (IO_25_15)
LCD_DB1: J1201.31 (DB1), U501.K15 (IO_L24P_T3_RS1_15)
LCD_DB2: J1201.30 (DB2), U501.J15 (IO_L24N_T3_RS0_15)
LCD_DB3: J1201.29 (DB3), U501.H15 (IO_L19N_T3_A21_VREF_15)
LCD_DB4: J1201.28 (DB4), U501.G16 (IO_L13N_T2_MRCC_15)
LCD_DB5: J1201.27 (DB5), U501.F16 (IO_L14N_T2_SRCC_15)
LCD_DB6: J1201.26 (DB6), U501.F15 (IO_L14P_T2_SRCC_15)
LCD_DB7: J1201.25 (DB7), U501.E16 (IO_L11N_T1_SRCC_15)
LCD_DB8: J1201.24 (DB8), U501.E15 (IO_L11P_T1_SRCC_15)
LCD_DB9: J1201.23 (DB9), U501.D15 (IO_L12P_T1_MRCC_15)
LCD_DB10: J1201.22 (DB10), U501.L18 (IO_L4P_T0_D04_14)
LCD_DB11: J1201.21 (DB11), U501.K17 (IO_L1P_T0_D00_MOSI_14)
LCD_DB12: J1201.20 (DB12), U501.J17 (IO_L23P_T3_FOE_B_15)
LCD_DB13: J1201.19 (DB13), U501.J18 (IO_L23N_T3_FWE_B_15)
LCD_DB14: J1201.18 (DB14), U501.H17 (IO_L18P_T2_A24_15)
LCD_DB15: J1201.17 (DB15), U501.H16 (IO_L13P_T2_MRCC_15)
LCD_DB16: J1201.16 (DB16), U501.G18 (IO_L22P_T3_A17_15)
LCD_DB17: J1201.15 (DB17), U501.G17 (IO_L18N_T2_A23_15)
LCD_DOTCLK: J1201.13 (DOTCLK), U501.E17 (IO_L16P_T2_A28_15)
LCD_D/~CX: J1201.37 (D/CX), U401.9 (GPIO16)
LCD_HSYNC: J1201.12 (HSYNC), U501.E18 (IO_L21P_T3_DQS_15)
LCD_VSYNC: J1201.11 (VSYNC), U501.D17 (IO_L16N_T2_A27_15)
LCD_~CS: J1201.38 (CSX), U401.8 (GPIO15)
LCD_~RST: J1201.10 (RESET), U401.7 (GPIO7)
MCU_~IRQ: J403.1, JP1401.2 (B), JP1402.2 (B), Q1601.3 (D), R408.2, U201.5 (~ALRT), U401.38 (GPIO2), U501.J3 (IO_L22P_T3_35), U1501.1 (~INT)
SDRAM_0_~CS: U501.V1 (IO_L7N_T1_34), U1301.19 (~CS)
SDRAM_A0: U501.R3 (IO_L11P_T1_SRCC_34), U1301.23 (A0)
SDRAM_A1: U501.T3 (IO_L11N_T1_SRCC_34), U1301.24 (A1)
SDRAM_A2: U501.T4 (IO_L12N_T1_MRCC_34), U1301.25 (A2)
SDRAM_A3: U501.R5 (IO_L19N_T3_VREF_34), U1301.26 (A3)
SDRAM_A4: U501.R6 (IO_L19P_T3_34), U1301.29 (A4)
SDRAM_A5: U501.T6 (IO_L23N_T3_34), U1301.30 (A5)
SDRAM_A6: U501.R7 (IO_L23P_T3_34), U1301.31 (A6)
SDRAM_A7: U501.R8 (IO_L24P_T3_34), U1301.32 (A7)
SDRAM_A8: U501.T8 (IO_L24N_T3_34), U1301.33 (A8)
SDRAM_A9: U501.U2 (IO_L9P_T1_DQS_34), U1301.34 (A9)
SDRAM_A10: U501.P4 (IO_L14P_T2_SRCC_34), U1301.22 (A10/AP)
SDRAM_A11: U501.V2 (IO_L9N_T1_DQS_34), U1301.35 (A11)
SDRAM_A12: U501.U3 (IO_L8N_T1_34), U1301.36 (A12)
SDRAM_BS0: U501.N4 (IO_L16N_T2_34), U1301.20 (BS0)
SDRAM_BS1: U501.P3 (IO_L14N_T2_SRCC_34), U1301.21 (BS1)
SDRAM_CKE: U501.U4 (IO_L8P_T1_34), U1301.37 (CKE)
SDRAM_CLK: U501.V4 (IO_L10N_T1_34), U1301.38 (CLK)
SDRAM_DQ0: U501.P2 (IO_L15P_T2_DQS_34), U1301.2 (DQ0)
SDRAM_DQ1: U501.N2 (IO_L3P_T0_DQS_34), U1301.4 (DQ1)
SDRAM_DQ2: U501.N1 (IO_L3N_T0_DQS_34), U1301.5 (DQ2)
SDRAM_DQ3: U501.M2 (IO_L4N_T0_34), U1301.7 (DQ3)
SDRAM_DQ4: U501.M1 (IO_L1N_T0_34), U1301.8 (DQ4)
SDRAM_DQ5: U501.L1 (IO_L1P_T0_34), U1301.10 (DQ5)
SDRAM_DQ6: U501.M3 (IO_L4P_T0_34), U1301.11 (DQ6)
SDRAM_DQ7: U501.M4 (IO_L16P_T2_34), U1301.13 (DQ7)
SDRAM_DQ8: U501.V5 (IO_L10P_T1_34), U1301.42 (DQ8)
SDRAM_DQ9: U501.U6 (IO_L22N_T3_34), U1301.44 (DQ9)
SDRAM_DQ10: U501.V6 (IO_L20N_T3_34), U1301.45 (DQ10)
SDRAM_DQ11: U501.U7 (IO_L22P_T3_34), U1301.47 (DQ11)
SDRAM_DQ12: U501.V7 (IO_L20P_T3_34), U1301.48 (DQ12)
SDRAM_DQ13: U501.U8 (IO_25_34), U1301.50 (DQ13)
SDRAM_DQ14: U501.U9 (IO_L21P_T3_DQS_34), U1301.51 (DQ14)
SDRAM_DQ15: U501.V9 (IO_L21N_T3_DQS_34), U1301.53 (DQ15)
SDRAM_LDQM: U501.R1 (IO_L17P_T2_34), U1301.15 (LDQM)
SDRAM_UDQM: U501.T5 (IO_L12P_T1_MRCC_34), U1301.39 (UDQM)
SDRAM_~CAS: U501.T1 (IO_L17N_T2_34), U1301.17 (~CAS)
SDRAM_~RAS: U501.U1 (IO_L7P_T1_34), U1301.18 (~RAS)
SDRAM_~WE: U501.R2 (IO_L15N_T2_DQS_34), U1301.16 (~WE)
SPI2_CLK: J404.1, J1201.36 (WRX(SCL)), R412.2, U501.E9 (CCLK_0), U501.F4 (IO_L13P_T2_MRCC_35)
SPI2_D2: R415.2, U501.G2 (IO_L15N_T2_DQS_35)
SPI2_D3: R409.2, U501.H1 (IO_L17P_T2_35)
SPI2_PICO/D0: J404.2, J1201.34 (SDA), R411.2, U501.H2 (IO_L15P_T2_DQS_35), U501.K18 (IO_L1N_T0_D01_DIN_14)
SPI2_POCI/D1: J404.3, J1201.33 (SDO), R413.2, U501.G1 (IO_L17N_T2_35)
SRAM_A0: U501.N17 (IO_L9P_T1_DQS_14), U1302.1 (A0)
SRAM_A1: U501.M17 (IO_L10N_T1_D15_14), U1302.2 (A1)
SRAM_A2: U501.M18 (IO_L4N_T0_D05_14), U1302.3 (A2)
SRAM_A3: U501.T9 (IO_L24P_T3_A01_D17_14), U1302.4 (A3)
SRAM_A4: U501.T10 (IO_L24N_T3_A00_D16_14), U1302.5 (A4)
SRAM_A5: U501.P15 (IO_L13P_T2_MRCC_14), U1302.18 (A5)
SRAM_A6: U501.N16 (IO_L11N_T1_SRCC_14), U1302.19 (A6)
SRAM_A7: U501.N15 (IO_L11P_T1_SRCC_14), U1302.20 (A7)
SRAM_A8: U501.M16 (IO_L10P_T1_D14_14), U1302.21 (A8)
SRAM_A9: U501.L16 (IO_L3N_T0_DQS_EMCCLK_14), U1302.22 (A9)
SRAM_A10: U501.V12 (IO_L20N_T3_A07_D23_14), U1302.23 (A10)
SRAM_A11: U501.U11 (IO_L19N_T3_A09_D25_VREF_14), U1302.24 (A11)
SRAM_A12: U501.V11 (IO_L21N_T3_DQS_A06_D22_14), U1302.25 (A12)
SRAM_A13: U501.V10 (IO_L21P_T3_DQS_14), U1302.26 (A13)
SRAM_A14: U501.U12 (IO_L20P_T3_A08_D24_14), U1302.27 (A14)
SRAM_A15: U501.R18 (IO_L7P_T1_D09_14), U1302.42 (A15)
SRAM_A16: U501.P17 (IO_L12P_T1_MRCC_14), U1302.43 (A16)
SRAM_A17: U501.P18 (IO_L9N_T1_DQS_D13_14), U1302.44 (A17)
SRAM_IO0: U501.R11 (IO_0_14), U1302.7 (IO0)
SRAM_IO1: U501.R12 (IO_L5P_T0_D06_14), U1302.8 (IO1)
SRAM_IO2: U501.T13 (IO_L23P_T3_A03_D19_14), U1302.9 (IO2)
SRAM_IO3: U501.R13 (IO_L5N_T0_D07_14), U1302.10 (IO3)
SRAM_IO4: U501.T14 (IO_L14P_T2_SRCC_14), U1302.13 (IO4)
SRAM_IO5: U501.T15 (IO_L14N_T2_SRCC_14), U1302.14 (IO5)
SRAM_IO6: U501.T16 (IO_L15N_T2_DQS_DOUT_CSO_B_14), U1302.15 (IO6)
SRAM_IO7: U501.R16 (IO_L15P_T2_DQS_RDWR_B_14), U1302.16 (IO7)
SRAM_IO8: U501.U13 (IO_L23N_T3_A02_D18_14), U1302.29 (IO8)
SRAM_IO9: U501.V14 (IO_L22N_T3_A04_D20_14), U1302.30 (IO9)
SRAM_IO10: U501.U14 (IO_L22P_T3_A05_D21_14), U1302.31 (IO10)
SRAM_IO11: U501.V15 (IO_L16P_T2_CSI_B_14), U1302.32 (IO11)
SRAM_IO12: U501.V16 (IO_L16N_T2_A15_D31_14), U1302.35 (IO12)
SRAM_IO13: U501.U16 (IO_L18P_T2_A12_D28_14), U1302.36 (IO13)
SRAM_IO14: U501.V17 (IO_L18N_T2_A11_D27_14), U1302.37 (IO14)
SRAM_IO15: U501.U18 (IO_L17N_T2_A13_D29_14), U1302.38 (IO15)
SRAM_~CE: U501.R10 (IO_25_14), U1302.6 (~CE)
SRAM_~LB: U501.U17 (IO_L17P_T2_A14_D30_14), U1302.39 (~LB)
SRAM_~OE: U501.R17 (IO_L12N_T1_MRCC_14), U1302.41 (~OE)
SRAM_~UB: U501.T18 (IO_L7N_T1_D10_14), U1302.40 (~UB)
SRAM_~WE: U501.R15 (IO_L13N_T2_MRCC_14), U1302.17 (~WE)
SW_Cartridge: R1803.1, U501.D18 (IO_L21N_T3_DQS_A18_15)
VBUS: C202.1, D401.4 (K3), D401.7 (K3), J401.A4 (VBUS), J401.A9 (VBUS), J401.B4 (VBUS), J401.B9 (VBUS), U202.13 (IN)
VGB: C1901.2, C1902.2, C1905.2, C1907.2, C1908.2, C1910.2, C1911.2, C2001.2, C2003.2, C2008.2, C2010.2, J1901.1 (VDD), J2001.1 (VDD), R1903.1, R2001.1, R2006.1, R2007.1, R2008.1, R2009.1, TP1801.1, U1801.1 (OUT), U1802.1 (OUT), U1901.6 (VCCB), U1902.7 (VCCB), U1902.18 (VCCB), U1903.6 (VCCB), U1904.7 (VCCB), U1904.18 (VCCB), U2001.6 (VCCB), U2002.6 (VCCB), U2003.6 (VCCB), U2004.6 (VCCB)
VIBRATE_EN: R1401.1, R1402.1, U501.E7 (IO_L6P_T0_35)
VSYS: C205.1, C302.1, C304.1, C309.1, C312.1, C315.1, C1605.1, C1606.2, C1607.1, C1608.2, L302.1, Q202.3 (D), R209.1, R309.1, TP203.1, U301.3 (VIN), U302.7 (VIN), U303.3 (VIN), U304.3 (VIN), U304.4 (EN), U306.1 (IN), U1601.21 (SPLVDD), U1601.24 (SPRVDD)
VSYS_ALWAYS: C203.1, C206.1, C1404.2, Q202.2 (S), R205.1, R207.1, R208.1, R213.1, TP202.1, U202.10 (OUT), U202.11 (OUT), U1402.8 (VDD)
~POWER_SW: R211.2, U401.39 (GPIO1)
~VBUS_PGOOD: U202.7 (~PGOOD), U401.34 (GPIO41/MTDI)
